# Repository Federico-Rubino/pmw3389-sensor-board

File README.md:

View this project on [CADLAB.io](https://cadlab.io/project/29776). 

# pmw3389-sensor-board

The repo contain the KiCad project for a custom PCB to use the PixArt pmw3389dm-T3QU. The board needs either 5V and 3V to be used.

# Usage

Clone this repo on your local machine and open the project using KiCad.

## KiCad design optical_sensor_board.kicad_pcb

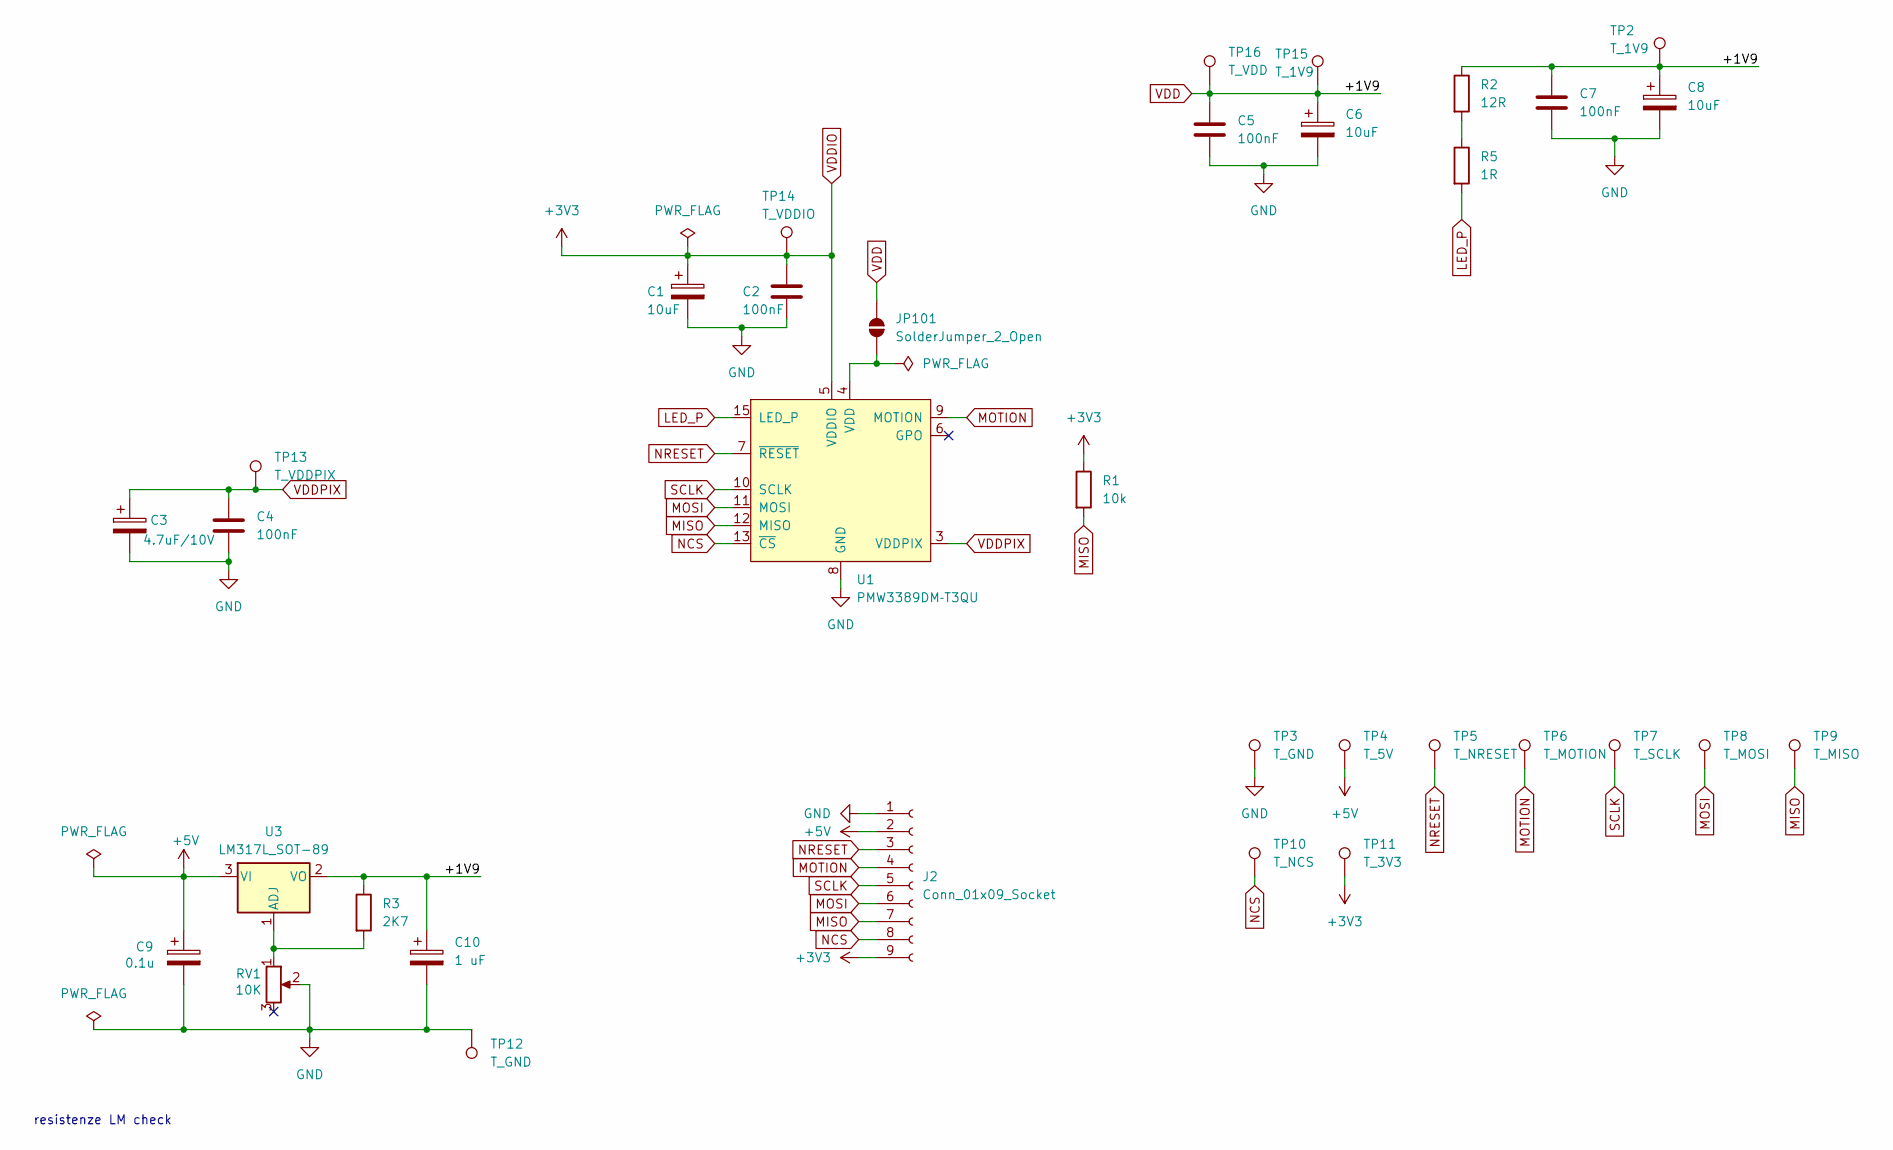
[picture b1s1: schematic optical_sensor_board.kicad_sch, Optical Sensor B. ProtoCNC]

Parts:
C1, C6, C8: 10uF; LargePad_CP_Radial_D6.3mm_P2.50mm
C2, C4, C5, C7: 100nF; LargePad_C_Disc_D5.0mm_W2.5mm_P5.00mm
C3: 4.7uF/10V; LargePad_CP_Radial_D6.3mm_P2.50mm
C9: 0.1u; LargePad_CP_Radial_D5.0mm_P2.00mm
C10: 1 uF; LargePad_CP_Radial_D5.0mm_P2.00mm
J2: Conn_01x09_Socket; LargePad_PinHeader_1x09_P2.54mm_Vertical
JP101: SolderJumper_2_Open; SolderJumper-2_P1.3mm_Open_TrianglePad1.0x1.5mm
R1: 10k; LargePad_R_Axial_DIN0207_L6.3mm_D2.5mm_P10.16mm_Horizontal
R2: 12R; LargePad_R_Axial_DIN0207_L6.3mm_D2.5mm_P10.16mm_Horizontal
R3: 2K7; LargePad_R_Axial_DIN0207_L6.3mm_D2.5mm_P10.16mm_Horizontal
R5: 1R; LargePad_R_Axial_DIN0207_L6.3mm_D2.5mm_P10.16mm_Horizontal
RV1: 10K; LargerPad_P160
TP2, TP15: T_1V9; TestPoint_Pad_1.0x1.0mm
TP3, TP12: T_GND; TestPoint_Pad_1.0x1.0mm
TP4: T_5V; TestPoint_Pad_1.0x1.0mm
TP5: T_NRESET; TestPoint_Pad_1.0x1.0mm
TP6: T_MOTION; TestPoint_Pad_1.0x1.0mm
TP7: T_SCLK; TestPoint_Pad_1.0x1.0mm
TP8: T_MOSI; TestPoint_Pad_1.0x1.0mm
TP9: T_MISO; TestPoint_Pad_1.0x1.0mm
TP10: T_NCS; TestPoint_Pad_1.0x1.0mm
TP11: T_3V3; TestPoint_Pad_1.0x1.0mm
TP13: T_VDDPIX; TestPoint_Pad_1.0x1.0mm
TP14: T_VDDIO; TestPoint_Pad_1.0x1.0mm
TP16: T_VDD; TestPoint_Pad_1.0x1.0mm
U1: PMW3389DM‐T3QU; LargePad_PXI-DIP-16
U3: LM317L_SOT-89; TO-220-3_Vertical

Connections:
+5V: C9.1, J2.2, TP4.1, U3.3 (VI)
GND: C1.2, C2.2, C3.2, C4.2, C5.2, C6.2, C7.2, C8.2, C9.2, C10.2, J2.1, RV1.2, TP3.1, TP12.1, U1.8 (GND)
LED_P: R5.2, U1.15 (LED_P)
MISO: J2.7, R1.2, TP9.1, U1.12 (MISO)
MOSI: J2.6, TP8.1, U1.11 (MOSI)
MOTION: J2.4, TP6.1, U1.9 (MOTION)
NCS: J2.8, TP10.1, U1.13 (~CS)
NRESET: J2.3, TP5.1, U1.7 (~RESET)
unnamed: JP101.2 (B), U1.4 (VDD)
unnamed: R2.2, R5.1
unnamed: R3.2, RV1.1, U3.1 (ADJ)
SCLK: J2.5, TP7.1, U1.10 (SCLK)
VDD: C5.1, C6.1, C7.1, C8.1, C10.1, JP101.1 (A), R2.1, R3.1, TP2.1, TP15.1, TP16.1, U3.2 (VO)
VDDIO: C1.1, C2.1, J2.9, R1.1, TP11.1, TP14.1, U1.5 (VDDIO)
VDDPIX: C3.1, C4.1, TP13.1, U1.3 (VDDPIX)

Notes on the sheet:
resistenze LM check

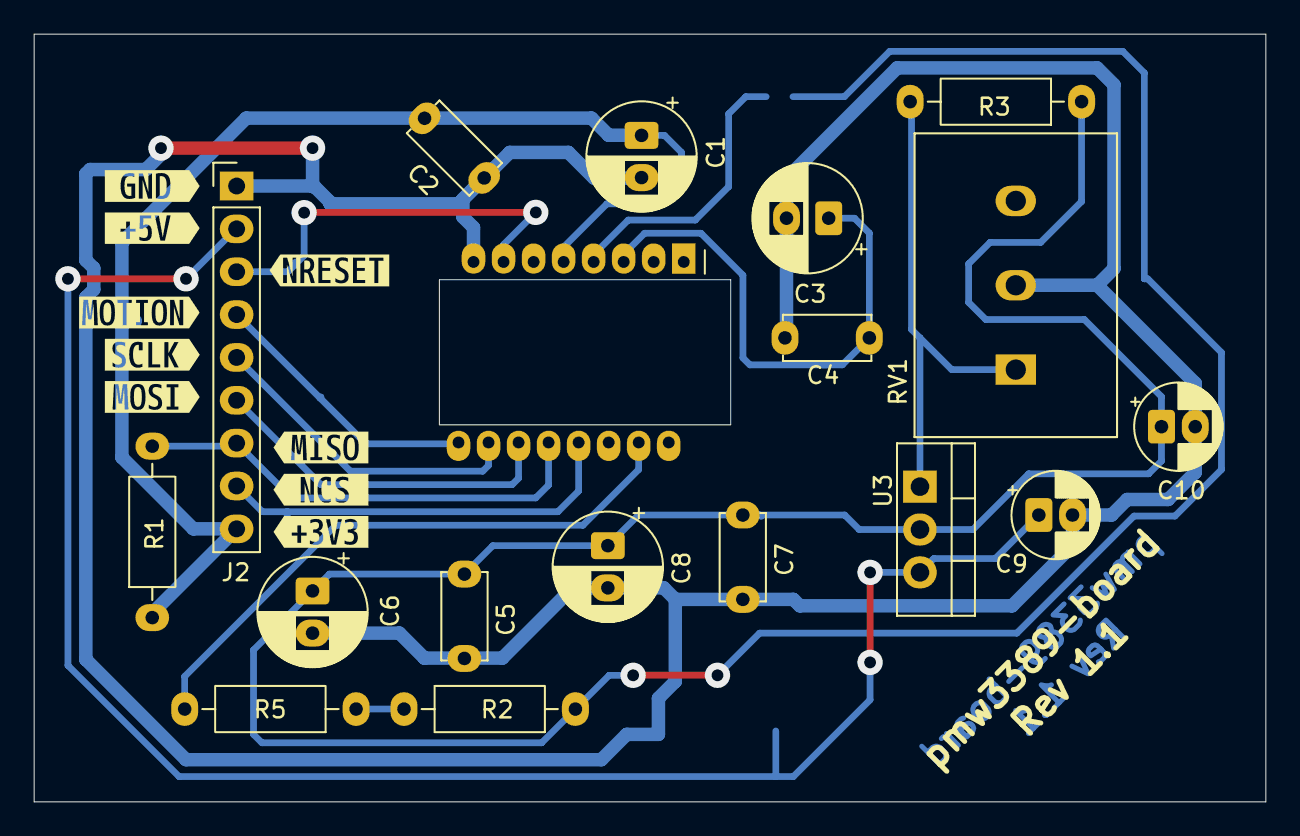
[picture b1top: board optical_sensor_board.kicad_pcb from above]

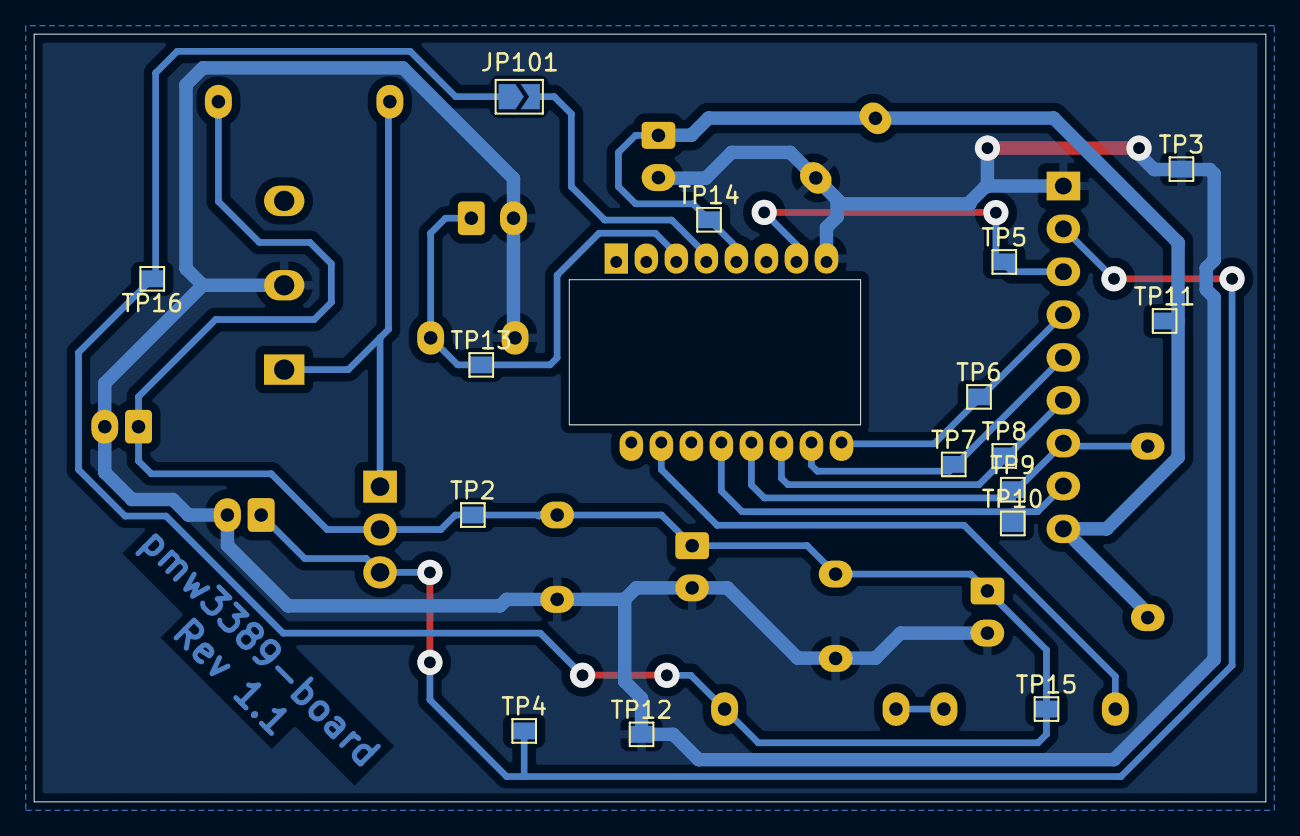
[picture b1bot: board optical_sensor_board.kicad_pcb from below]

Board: 2 copper layers, 73.0 x 45.5 mm, 43 parts (16 on the bottom side), 15 nets.

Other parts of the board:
kibuzzard-692FFC6C: G***; kibuzzard-692FFC6C
kibuzzard-692FFFAD: G***; kibuzzard-692FFFAD
kibuzzard-692FFFD7: G***; kibuzzard-692FFFD7
kibuzzard-692FFFF6: G***; kibuzzard-692FFFF6
kibuzzard-69300A7E: G***; kibuzzard-69300A7E
kibuzzard-69300AAA: G***; kibuzzard-69300AAA
kibuzzard-69300B41: G***; kibuzzard-69300B41
kibuzzard-69300011: G***; kibuzzard-69300011
kibuzzard-69303597: G***; kibuzzard-69303597

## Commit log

2025-12-01 Init commit
2025-12-01 Aggiunta copper-area + modifiche a schematico e master
    Design:
    - Spostate le tracce sul bottom e i ponti sul top layer
    - Aggiunta la Copper Area sul bottom layer
    - Sistemate le serigrafie
    Schematico:
    - Corretti gli errori del ERC aggiungendo i PWR_FLAG
2025-12-01 add potentiometer in LM317 circuit
2025-12-01 add CERN OHL Permissive License
2025-12-01 potentiometer footprint + potentiometer routing
2025-12-01 copper area
2025-12-01 Backlink to CADLAB.io has been added.
2025-12-01 pmw3386Board RV1 text
2025-12-01 copper GND plane
2025-12-01 TestPoint in Schematic
2025-12-02 add Footprint TestPoint
2025-12-02 start TestPoint routing
2025-12-02 TestPoint routed
2025-12-03 Modificato graficamente lo schematico + moidifiche al PCB
    - Sistemato graficamente lo schema
    - Corretto il testo del PCB
2025-12-03 SilkScreen pin name
2025-12-03 Correct trimmer footprint
2025-12-03 modified SilkScreen for pin MOTION
2025-12-05 New potentiometer footprint + pin Labels
2025-12-05 Modified some componets position
2025-12-05 Re-runned DEC and corrected some errors
2025-12-05 drc ok + pdf for PnP
2025-12-05 Added a solder-jumer in series to the PS of the chip
2025-12-05 Modified some traks of the PCB + exported new PDF for mastering
2026-02-16 Update README with project details and usage
    Added project description and usage instructions.
